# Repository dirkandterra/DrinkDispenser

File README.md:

# DrinkDispenser
Taking a Keurig style coffee maker and turning it into a drink dispenser

-Requires HX711 arduino library

-Requires ESPAsyncWebServer and AsyncTCP libraries

-Requires SparkFun Micro OLED Library 

	!!!!!!must change "swap" keyword to something else as there is a conflict with wifi software!!!!!!

-Change #defines in CustomInfo.h file to set internal and external wifi ssid and pwd

-Tries to connect to external wifi, fires up its own wifi if it fails.  IP 192.168.4.1

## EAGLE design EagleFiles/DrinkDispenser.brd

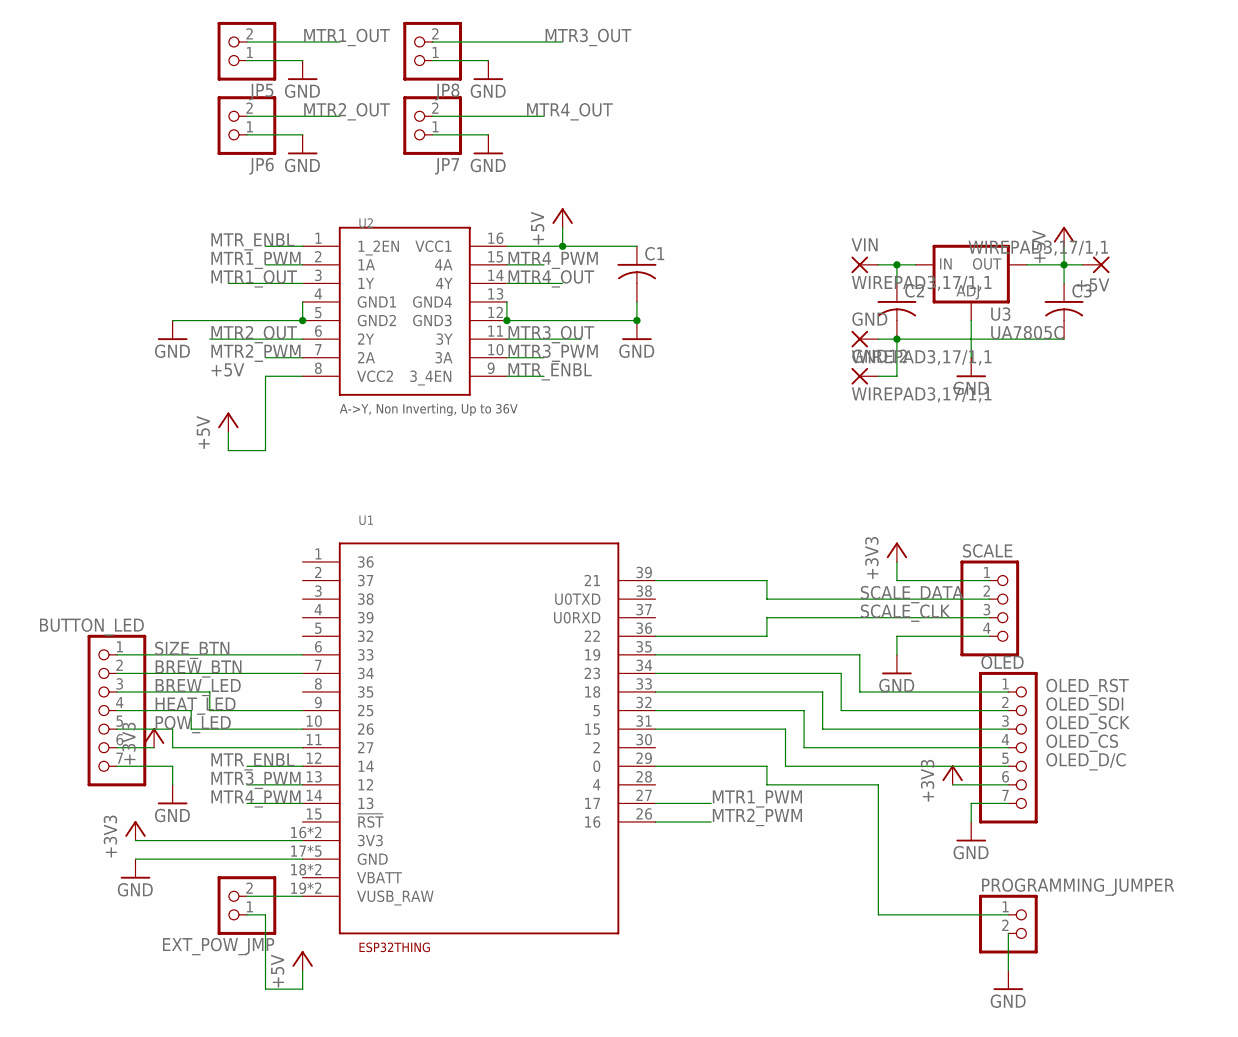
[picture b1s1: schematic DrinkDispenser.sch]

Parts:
+5V: WIREPAD3,17/1,1; 3,17/1,1
BUTTON_LED: PINHD-1X7; 1X07
C1, C2, C3: C-USC0805; C0805
EXT_POW_JMP: PINHD-1X2; 1X02
GND, GND12: WIREPAD3,17/1,1; 3,17/1,1
JP5, JP6, JP7, JP8: PINHD-1X2; 1X02
OLED: PINHD-1X7; 1X07
PROGRAMMING_JUMPER: PINHD-1X2; 1X02
SCALE: PINHD-1X4; 1X04
U1: ESP32THING
U2: L293DDIP16; DIP16_7.62MM
U3: UA7805C; TO-263
VIN: WIREPAD3,17/1,1; 3,17/1,1

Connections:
+3V3: BUTTON_LED.6, OLED.6, SCALE.1, U1.16 (3V3), U1.25 (3V3)
+5V: +5V.1, C1.1, C3.1, EXT_POW_JMP.1, U2.8 (VCC2), U2.16 (VCC1), U3.3 (OUT)
BREW_BTN: BUTTON_LED.2, U1.7 (34)
BREW_LED: BUTTON_LED.3, U1.9 (25)
GND: BUTTON_LED.7, C1.2, C2.2, C3.2, GND.1, GND12.1, JP5.1, JP6.1, JP7.1, JP8.1, OLED.7, PROGRAMMING_JUMPER.2, SCALE.4, U1.17 (GND), U1.20 (GND), U1.21 (GND), U1.24 (GND), U1.40 (GND), U2.4 (GND1), U2.5 (GND2), U2.12 (GND3), U2.13 (GND4), U3.2 (ADJ), U3.4 (ADJ)
HEAT_LED: BUTTON_LED.4, U1.10 (26)
MTR1_OUT: JP5.2, U2.3 (1Y)
MTR1_PWM: U1.27 (17), U2.2 (1A)
MTR2_OUT: JP6.2, U2.6 (2Y)
MTR2_PWM: U1.26 (16), U2.7 (2A)
MTR3_OUT: JP8.2, U2.11 (3Y)
MTR3_PWM: U1.13 (12), U2.10 (3A)
MTR4_OUT: JP7.2, U2.14 (4Y)
MTR4_PWM: U1.14 (13), U2.15 (4A)
MTR_ENBL: U1.12 (14), U2.1 (1_2EN), U2.9 (3_4EN)
unnamed: C2.1, U3.1 (IN), VIN.1
unnamed: EXT_POW_JMP.2, U1.19 (VUSB_RAW), U1.23 (VUSB_RAW)
unnamed: PROGRAMMING_JUMPER.1, U1.29 (0)
OLED_CS: OLED.4, U1.32 (5)
OLED_D/C: OLED.5, U1.31 (15)
OLED_RST: OLED.1, U1.35 (19)
OLED_SCK: OLED.3, U1.33 (18)
OLED_SDI: OLED.2, U1.34 (23)
POW_LED: BUTTON_LED.5, U1.11 (27)
SCALE_CLK: SCALE.3, U1.36 (22)
SCALE_DATA: SCALE.2, U1.39 (21)
SIZE_BTN: BUTTON_LED.1, U1.6 (33)

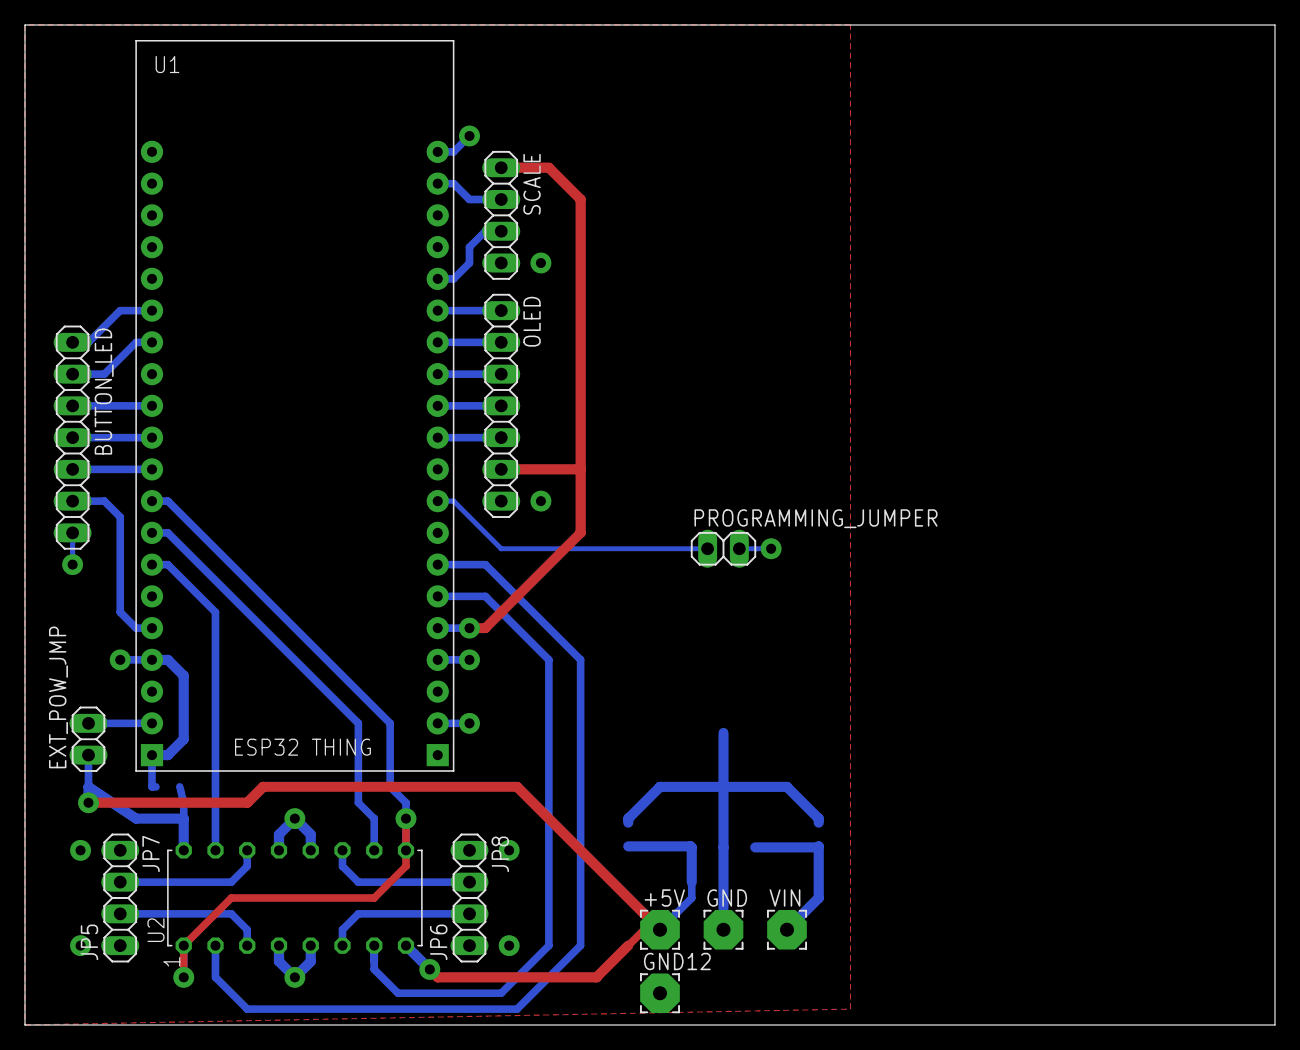
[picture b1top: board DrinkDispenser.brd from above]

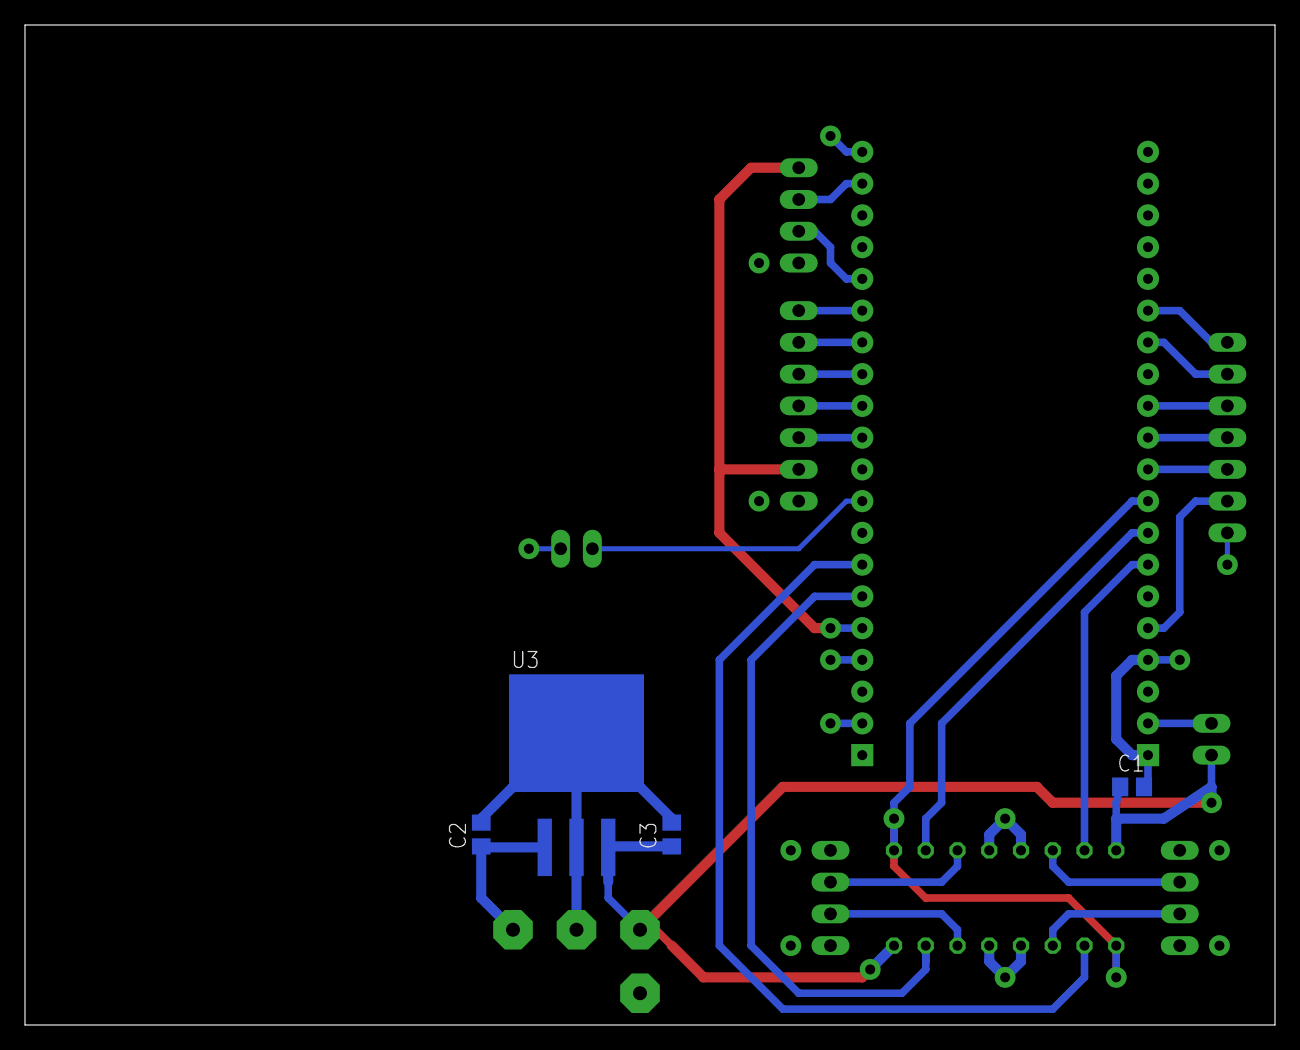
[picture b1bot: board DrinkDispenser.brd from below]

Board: 2 copper layers, 100.0 x 80.0 mm, 19 parts (4 on the bottom side), 27 nets.

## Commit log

2019-11-12 Added ino file and eagle files
2019-11-12 Test commit
2019-11-12 Rename .ino to match folder name
2019-11-25 Try out EEPROM code and tweaked cal
2020-02-04 -Added Async web server operations to routine -Added another decimal accuracy to product cal -Added CustomInfo.h file to house ssid, pwd, and other sensitive info
2020-02-04 Formatting on Readme fixed
2021-07-11 Update DrinkDispenserArduinoESP32.ino
    -Added factory reset on Wifi
    -Added error trap for current weight being less than starting weight (removing cup before weighing is done)
    -Other website page changes
2021-07-11 Update DrinkDispenserArduinoESP32.ino
    Print version on serial debug
